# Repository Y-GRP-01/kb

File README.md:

# 50-50 Split Wireless Keyboard

This branch covers the WIP for this project.

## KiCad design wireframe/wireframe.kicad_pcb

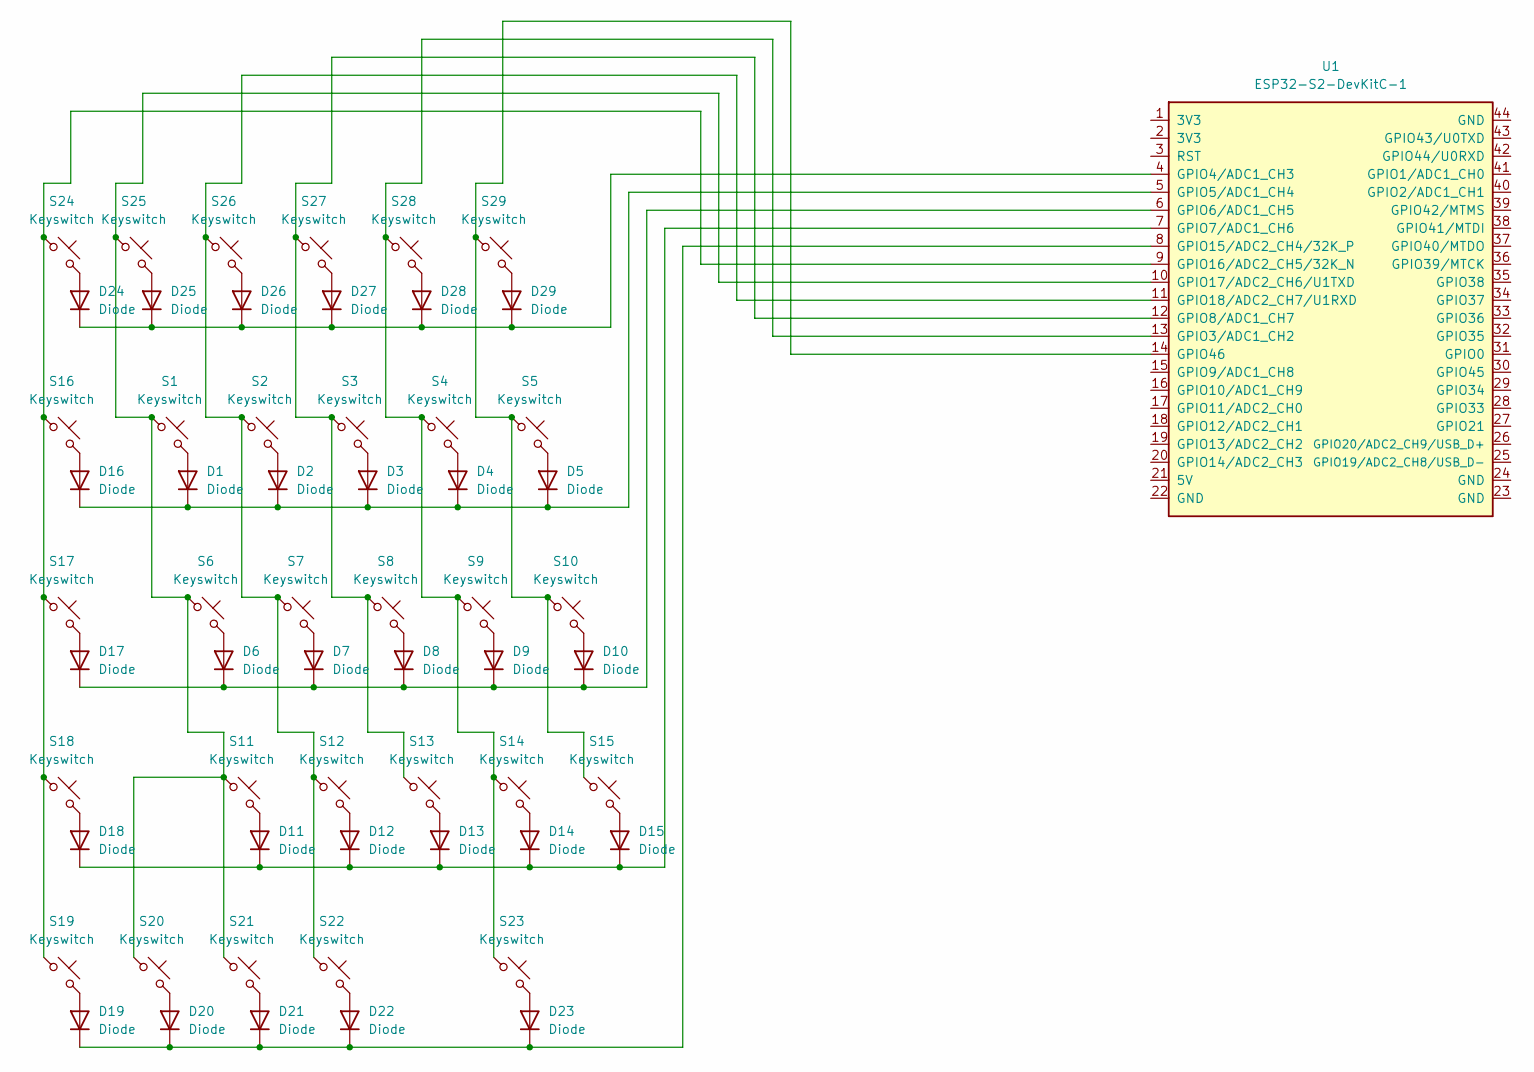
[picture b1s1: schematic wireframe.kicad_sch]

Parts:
D1, D2, D3, D4, D5, D6, D7, D8, D9, D10, D11, D12, D13, D14, D15, D16, D17, D18, D19, D20, D21, D22, D23, D24, D25, D26, D27, D28, D29: Diode; Diode_DO-35
S1, S2, S3, S4, S5, S6, S7, S8, S9, S10, S11, S12, S13, S14, S15, S19, S20, S21, S22, S24, S25, S26, S27, S28, S29: Keyswitch; MX_PCB_1.00u
S16: Keyswitch; MX_PCB_1.50u
S17: Keyswitch; MX_PCB_2.00u
S18: Keyswitch; MX_PCB_2.50u
S23: Keyswitch; MX_PCB_3.00u
U1: ESP32-S2-DevKitC-1

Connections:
unnamed: D1.2 (A), S1.2
unnamed: D1.1 (K), D2.1 (K), D3.1 (K), D4.1 (K), D5.1 (K), D16.1 (K), U1.5 (GPIO5/ADC1_CH4)
unnamed: D2.2 (A), S2.2
unnamed: D3.2 (A), S3.2
unnamed: D4.2 (A), S4.2
unnamed: D5.2 (A), S5.2
unnamed: D6.2 (A), S6.2
unnamed: D7.2 (A), S7.2
unnamed: D8.2 (A), S8.2
unnamed: D9.2 (A), S9.2
unnamed: D10.2 (A), S10.2
unnamed: D6.1 (K), D7.1 (K), D8.1 (K), D9.1 (K), D10.1 (K), D17.1 (K), U1.6 (GPIO6/ADC1_CH5)
unnamed: D11.2 (A), S11.2
unnamed: D11.1 (K), D12.1 (K), D13.1 (K), D14.1 (K), D15.1 (K), D18.1 (K), U1.7 (GPIO7/ADC1_CH6)
unnamed: D12.2 (A), S12.2
unnamed: D13.2 (A), S13.2
unnamed: D14.2 (A), S14.2
unnamed: D15.2 (A), S15.2
unnamed: D16.2 (A), S16.2
unnamed: D17.2 (A), S17.2
unnamed: D18.2 (A), S18.2
unnamed: D19.2 (A), S19.2
unnamed: D19.1 (K), D20.1 (K), D21.1 (K), D22.1 (K), D23.1 (K), U1.8 (GPIO15/ADC2_CH4/32K_P)
unnamed: D20.2 (A), S20.2
unnamed: D21.2 (A), S21.2
unnamed: D22.2 (A), S22.2
unnamed: D23.2 (A), S23.2
unnamed: D24.2 (A), S24.2
unnamed: D24.1 (K), D25.1 (K), D26.1 (K), D27.1 (K), D28.1 (K), D29.1 (K), U1.4 (GPIO4/ADC1_CH3)
unnamed: D25.2 (A), S25.2
unnamed: D26.2 (A), S26.2
unnamed: D27.2 (A), S27.2
unnamed: D28.2 (A), S28.2
unnamed: D29.2 (A), S29.2
unnamed: S4.1, S9.1, S14.1, S23.1, S28.1, U1.13 (GPIO3/ADC1_CH2)
unnamed: S3.1, S8.1, S13.1, S27.1, U1.12 (GPIO8/ADC1_CH7)
unnamed: S16.1, S17.1, S18.1, S19.1, S24.1, U1.9 (GPIO16/ADC2_CH5/32K_N)
unnamed: S1.1, S6.1, S11.1, S20.1, S21.1, S25.1, U1.10 (GPIO17/ADC2_CH6/U1TXD)
unnamed: S2.1, S7.1, S12.1, S22.1, S26.1, U1.11 (GPIO18/ADC2_CH7/U1RXD)
unnamed: S5.1, S10.1, S15.1, S29.1, U1.14 (GPIO46)

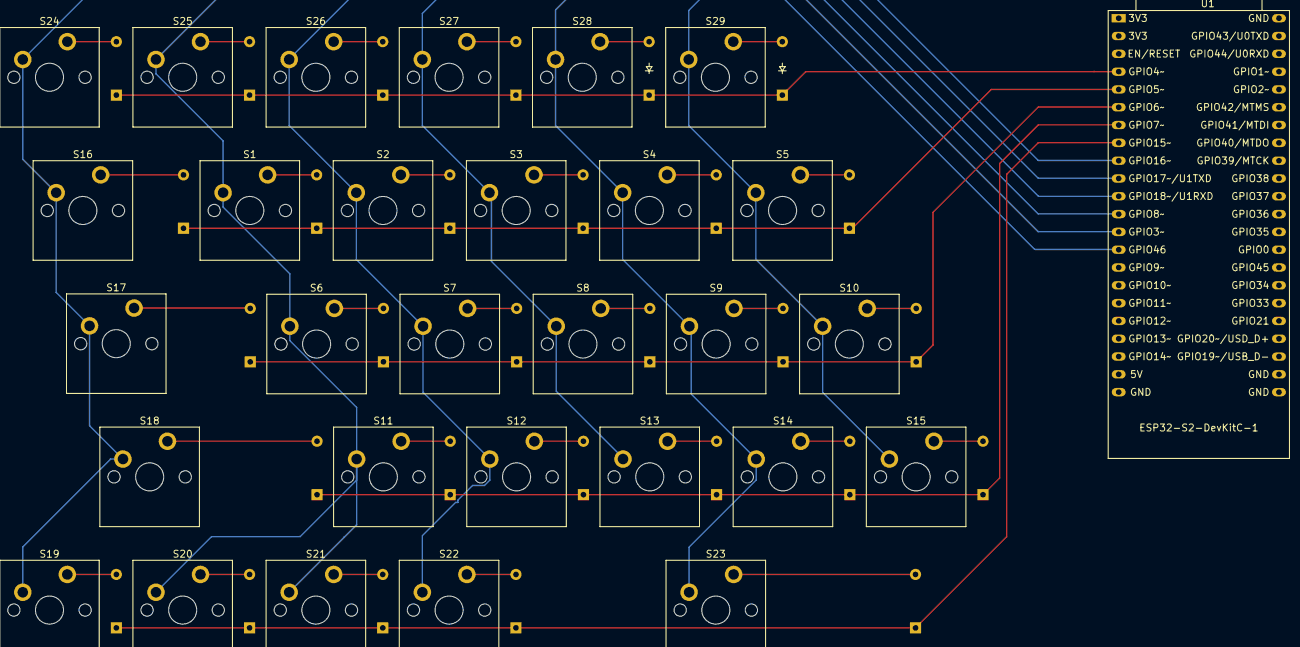
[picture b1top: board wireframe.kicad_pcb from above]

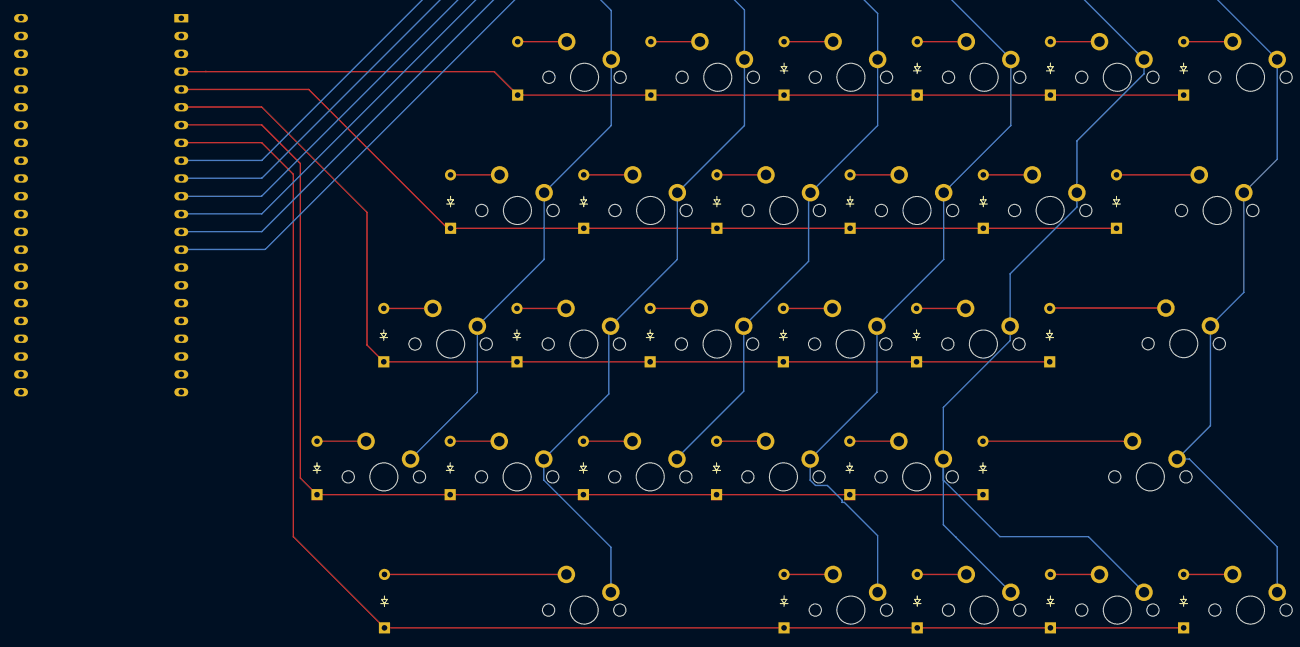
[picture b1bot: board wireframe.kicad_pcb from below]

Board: 2 copper layers, 59 parts (27 on the bottom side), 40 nets.

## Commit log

2025-09-11 Add development branch README
2025-09-21 [+] Add development documentation
2025-09-21 [+] Add KiCad files
2025-09-22 Finalize layout and fully traced to ESP32
2025-09-29 code section
2025-10-24 Add fIles
